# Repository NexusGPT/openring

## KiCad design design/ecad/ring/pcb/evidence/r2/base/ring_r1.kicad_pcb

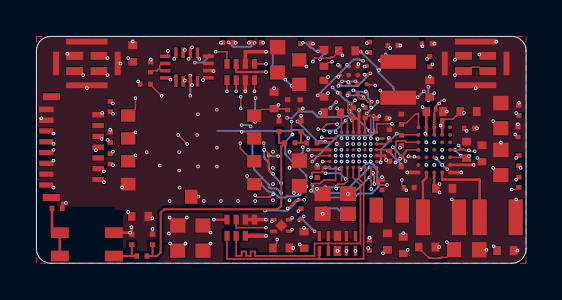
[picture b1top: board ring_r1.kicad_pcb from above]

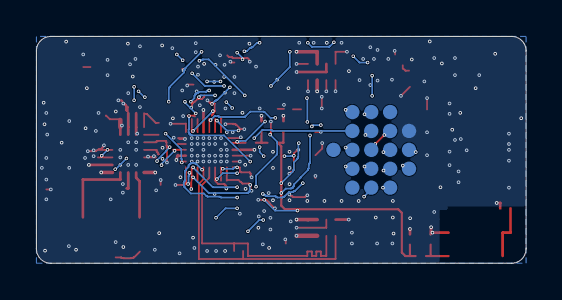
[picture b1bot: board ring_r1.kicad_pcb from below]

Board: 4 copper layers, 27.2 x 12.6 mm, 104 parts (19 on the bottom side), 91 nets.

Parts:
ANT1: 2450AT18D0100001E; ANT_Johanson_2450AT18D0100001E_3.2x1.6
C1, C2, C5, C61, C72, C80, C81, C82: 100nF; Chip_0201
C3: 1.2pF; Chip_0201
C4, C22, C74, C75, C78, C79, C83, C84: 10uF; Chip_0402
C6: 4.7uF; Chip_0201
C7, C10, C14: 2.2uF; Chip_0201
C11: 4.7uF; Chip_0402
C12: 0.5pF; Chip_0201
C13, C89: DNP; Chip_0201
C21, C26, C27: 4.7uF; Chip_0603
C23, C60, C85: 2.2uF; Chip_0402
C24, C25, C88: 10uF; Chip_0603
C28, C29: 22uF; Chip_0402
C31, C32: 1uF; Chip_0201
C35, C36: 1nF C0G; Chip_0402
C71: 1.0uF 25V; Chip_0402
C73: 1.0uF; Chip_0201
C76, C77: 1.0nF; Chip_0201
C86, C87: 1.0uF; Chip_0402
FB1: 120R@100MHz; Chip_0201
J1: FH35C-15S-0.3SHW(50); FPC_Hirose_FH35C-15S-0.3SHW
J_BAND_A: flex tail A (joystick side) 8 pads; J_BAND_A_BOARD
J_BAND_B: flex tail B (other side) 7 pads; J_BAND_B_BOARD
L1: 4.7uH; L_TDK_MLZ1608_1.6x0.8
L2: 3.6nH; Chip_0201
L3: 4.7nH; Chip_0201
L4: 3.3nH; Chip_0201
L10, L71, L72: 2.2uH; L_Murata_1269AS-H_2.5x2.0
LT1: 0R; Chip_0201
R1: 2.2R; Chip_0603
R2: 220R; Chip_0201
R31, R32, R61: 100R; Chip_0201
R57, R58: 4.7k; Chip_0201
R60, R63, R64, R65, R71: 47k; Chip_0201
R62, R66: 100k; Chip_0201
R72: 150k; Chip_0201
TP1, TP2, TP3, TP4, TP5, TP6, TP8, TP9, TP11, TP12, TP13, TP14, TP15, TP16, TP17, TP18, TP19, TP21, TP22: pad; TESTPAD_0.8
U1: nRF54LM20A; WLCSP-61_nRF54LM20A-CAAA
U2: nPM1304; WLCSP-35_nPM1304-CAAA
U3: CSNP32GCR01-BOW; LGA-9_CSNP32GCR01-BOW_8.0x6.2
U4: SGM38046; WLCSP-16_SGM38046_2.0x2.0_P0.5
U5, U6: SPK0641HT4H-1; LGA-8_Knowles_SPK0641HT4H-1_3.0x4.0
U9: TPD4E05U06; USON-10_TPD4E05U06DQA
U10: SN74AXC4T774; UQFN-16_SN74AXC4T774RSV_1.8x2.6
U11: TLV75530P 3.0V; X2SON-4_TLV755xxPDQN_1.0x1.0
X1: 32MHz; XTAL_Kyocera_CX2016DB_2.0x1.6
X2: 32.768kHz; XTAL_TXC_9HT11_2.0x1.2

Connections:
ANT1_NODE: L2.1, U1.C1
ANT2_NODE: C3.1, L2.2, L3.1
ANT3_NODE: C12.1, C89.1, L3.2, L4.1
ANT_TRIM: ANT1.2, ANT1.3, LT1.1
BTN_REC: J_BAND_A.5, U1.H2
DBG_RX: TP2.1, U1.B5
DBG_TX: TP1.1, U1.B4
DCC: L1.1, U1.A5
DECA: C7.1, C14.1, FB1.2, U1.A8, U1.B2
DECD: C6.1, FB1.1, L1.2, U1.A6
ELVDD: C25.1, J1.2, U4.D3
ELVSS: C28.1, C29.1, J1.1, U4.D4
GND: ANT1.4, C1.2, C2.2, C3.2, C4.2, C5.2, C6.2, C7.2, C10.2, C11.2, C12.2, C13.2, C14.2, C21.2, C22.2, C24.2, C25.2, C26.2, C27.2, C28.2, C29.2, C31.2, C32.2, C35.2, C36.2, C60.2, C61.2, C71.2, C72.2, C73.2, C74.2, C75.2, C76.2, C77.2, C78.2, C79.2, C80.2, C81.2, C82.2, C83.2, C84.2, C85.2, C86.2, C87.2, C88.2, C89.2, J1.13, J1.14, J1.15, J_BAND_A.6, J_BAND_A.8, J_BAND_B.2, J_BAND_B.7, LT1.2, R2.2, R62.2, R66.2, R71.2, R72.2, TP18.1, U1.A7, U1.D3, U1.E1, U1.F10, U2.A6, U2.A7, U2.E7, U3.4, U4.A3, U4.B2, U4.B3, U5.3, U5.5, U5.6, U5.7, U5.8, U6.5, U6.6, U6.7, U6.8, U9.3, U9.8, U10.6, U10.7, U10.8, U11.2, U11.5, X1.2
JOY_CENTER: TP22.1, U1.H4
JOY_DOWN: J_BAND_A.2, U1.G2
JOY_LEFT: J_BAND_A.3, U1.G1
JOY_RIGHT: J_BAND_A.4, U1.G10
JOY_UP: J_BAND_A.1, U1.H1
LCD_CS: J1.9, U1.F7
LCD_DCX: J1.11, U1.G7
LCD_MOSI: J1.12, U1.G8
LCD_RST: J1.8, U1.H5
LCD_SCK: J1.10, U1.G9
LCD_TE: J1.7, U1.D6
MIC1_DATA: R31.1, U5.1
MIC2_DATA: R32.1, U6.1
MIC_A_CLK: U1.F1, U5.2, U6.2
MIC_A_DATA: R31.2, R32.2, U1.F2
MIC_B_DATA: TP21.1, U1.D7
MOTOR: R61.1, U1.F6
MOT_EN: R61.2, R62.1, U11.3
NRESET: TP5.1, U1.E2
NTC: J_BAND_B.3, U2.D3
OLED_PWR_EN: R66.1, U1.E9, U4.C2
PMIC_INT: U1.D8, U2.D6
PMIC_SCL: R58.1, U1.E7, U2.E3
PMIC_SDA: R57.1, U1.B8, U2.E5
RF_FEED: ANT1.1, C13.1, L4.2
SDC_CS: R65.1, U3.2, U10.10
SDC_MISO: R60.1, U3.6, U10.9
SDC_MOSI: U3.5, U10.11
SDC_SCK: U3.3, U10.12
SD_CS: U1.D9, U10.3
SD_DAT1: R63.1, U3.7
SD_DAT2: R64.1, U3.1
SD_MISO: U1.D10, U10.4
SD_MOSI: U1.B10, U10.2
SD_SCK: U1.A9, U10.1
SGM_AVDD: C26.1, U4.D2
SGM_AVIN: C22.1, U4.A2
SGM_C1N: C23.2, U4.B4
SGM_C1P: C23.1, U4.A4
SGM_SW1: L10.1, U4.B1
SGM_SW2: L10.2, U4.C1
SGM_VON: C27.1, U4.C4
SGM_VOUT: C24.1, U4.D1
SHPHLD: TP19.1, U2.D4
SPARE_P1_00: TP6.1, U1.H10
SPARE_P1_02: TP8.1, U1.F8
SPARE_P1_14: TP9.1, U1.F4
SPARE_P1_30: TP11.1, U1.F9
SPARE_P2_00: TP12.1, U1.A10
SPARE_P2_03: TP13.1, U1.B9
SPARE_P3_03: TP14.1, U1.F5
SPARE_P3_04: TP15.1, U1.G5
SPARE_P3_05: TP16.1, U1.G4
SW1: L71.1, U2.B7
SW2: L72.1, U2.D7
SWDCLK: TP3.1, U1.D5
SWDIO: TP4.1, U1.E4
SWIRE: J1.6, U4.C3
TXRTUNE: R2.1, U1.G6
U1_VBUS: C11.1, R1.2, U1.H9
USB_DN: J_BAND_B.5, U1.H6, U9.2
USB_DP: J_BAND_B.6, U1.H7, U9.1
VBAT: C21.1, C83.1, C85.1, J_BAND_B.1, U2.D1, U2.D2, U4.A1, U11.4
VBUS: C71.1, C72.1, J_BAND_B.4, R1.1, U2.B1, U2.B2, U9.4, U9.5
VBUSOUT: C73.1, U2.C3
VDD_1V8: C1.1, C2.1, C4.1, C5.1, C78.1, C80.1, C81.1, J1.5, L71.2, R57.2, R58.2, TP17.1, U1.A4, U1.E10, U2.B4, U2.B6, U2.E4, U10.5, U10.14, U10.15, U10.16
VDD_3V0: C79.1, J1.4, L72.2, U2.B5, U2.C6
VDD_MIC: C31.1, C32.1, C35.1, C36.1, C86.1, U2.A4, U5.4, U6.3, U6.4
VDD_SD: C60.1, C61.1, C82.1, C87.1, R60.2, R63.2, R64.2, R65.2, U2.A5, U3.8, U10.13
VDD_USB_3V3: C10.1, U1.H8
VMOT: C84.1, J_BAND_A.7, U11.1
VSET1: R71.1, U2.E2
VSET2: R72.1, U2.E1
VSYS: C74.1, C75.1, C76.1, C77.1, C88.1, U2.C1, U2.C2, U2.C7
XC1: U1.A2, X1.1
XC2: U1.A1, X1.3
XL1: U1.B6, X2.1
XL2: U1.B7, X2.2

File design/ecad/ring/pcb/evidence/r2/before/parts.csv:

reference,symbol,value,mpn,footprint,sheet,dnp
U1,nRF54LM20A_CAAA,nRF54LM20A,NRF54LM20A-CAAA-R7,OpenRing:WLCSP-61_nRF54LM20A-CAAA,main,no
C4,C,10uF,GRM155R60J106ME15D,OpenRing:Chip_0402,main,no
C5,C,100nF,CL03A104KP3NNNC,OpenRing:Chip_0201,main,no
C1,C,100nF,CL03A104KP3NNNC,OpenRing:Chip_0201,main,no
C2,C,100nF,CL03A104KP3NNNC,OpenRing:Chip_0201,main,no
L1,L,4.7uH,MLZ1608M4R7WT000,OpenRing:L_TDK_MLZ1608_1.6x0.8,main,no
C6,C,4.7uF,GRM035R60J475ME15J,OpenRing:Chip_0201,main,no
FB1,FB,120R@100MHz,BLM03AG121SN1D,OpenRing:Chip_0201,main,no
C7,C,2.2uF,GRM033D80E225ME47D,OpenRing:Chip_0201,main,no
C14,C,2.2uF,GRM033D80E225ME47D,OpenRing:Chip_0201,main,no
C10,C,2.2uF,GRM033D80E225ME47D,OpenRing:Chip_0201,main,no
R1,R,2.2R,RC0603FR-072R2L,OpenRing:Chip_0603,main,no
C11,C,4.7uF,GRM155R61A475MEAAD,OpenRing:Chip_0402,main,no
R2,R,220R,RC0201FR-07220RL,OpenRing:Chip_0201,main,no
X1,XTAL_CX2016DB,32MHz,CX2016DB32000D0WZRC1,OpenRing:XTAL_Kyocera_CX2016DB_2.0x1.6,main,no
X2,XTAL_2PAD,32.768kHz,9HT11-32.768KDZC-T,OpenRing:XTAL_TXC_9HT11_2.0x1.2,main,no
L2,L,3.6nH,LQP03HQ3N6B02,OpenRing:Chip_0201,main,no
C3,C,1.2pF,GJM0335C1H1R2WB01D,OpenRing:Chip_0201,main,no
L3,L,4.7nH,LQP03HQ4N7H02,OpenRing:Chip_0201,main,no
C12,C,0.5pF,GJM0335C1ER50WB01D,OpenRing:Chip_0201,main,no
L4,L,3.3nH,LQP03HQ3N3B02,OpenRing:Chip_0201,main,no
C13,C,DNP,,OpenRing:Chip_0201,main,yes
ANT1,2450AT18D0100,2450AT18D0100001E,2450AT18D0100001E,OpenRing:ANT_Johanson_2450AT18D0100001E_3.2x1.6,main,no
LT1,R,0R,,OpenRing:Chip_0201,main,no
C89,C,DNP,,OpenRing:Chip_0201,main,yes
U2,nPM1304_CSP35,nPM1304,nPM1304-CAAA-R7,OpenRing:WLCSP-35_nPM1304-CAAA,power,no
C71,C,1.0uF 25V,GRM155R61E105KA12D,OpenRing:Chip_0402,power,no
C85,C,2.2uF,0402ZC225KAT2A,OpenRing:Chip_0402,power,no
C88,C,10uF,GRT188R61A106KE13D,OpenRing:Chip_0603,power,no
C86,C,1.0uF,GRM155R61E105KA12D,OpenRing:Chip_0402,power,no
C87,C,1.0uF,GRM155R61E105KA12D,OpenRing:Chip_0402,power,no
C72,C,100nF,CL03A104KP3NNNC,OpenRing:Chip_0201,power,no
C73,C,1.0uF,GRM033R60J105MEA2D,OpenRing:Chip_0201,power,no
C74,C,10uF,GRM155R60J106ME15D,OpenRing:Chip_0402,power,no
C75,C,10uF,GRM155R60J106ME15D,OpenRing:Chip_0402,power,no
C76,C,1.0nF,,OpenRing:Chip_0201,power,no
C77,C,1.0nF,,OpenRing:Chip_0201,power,no
L71,L,2.2uH,1269AS-H-2R2M=P2,OpenRing:L_Murata_1269AS-H_2.5x2.0,power,no
C78,C,10uF,GRM155R60J106ME15D,OpenRing:Chip_0402,power,no
L72,L,2.2uH,1269AS-H-2R2M=P2,OpenRing:L_Murata_1269AS-H_2.5x2.0,power,no
C79,C,10uF,GRM155R60J106ME15D,OpenRing:Chip_0402,power,no
C80,C,100nF,CL03A104KP3NNNC,OpenRing:Chip_0201,power,no
R71,R,47k,RC0201FR-0747KL,OpenRing:Chip_0201,power,no
R72,R,150k,RC0201FR-07150KL,OpenRing:Chip_0201,power,no
RT1,NTC,10k NTC,NCP15XH103F03RC,OpenRingBand:RT1_NTC_0402,band,no
BT1,CELL,4.35V 20-27mAh at US9 (17.6mAh min at US7) curved,Grepow custom,OpenRingBand:PRT1_Tabs,band,no
R57,R,4.7k,RC0201FR-074K7L,OpenRing:Chip_0201,power,no
R58,R,4.7k,RC0201FR-074K7L,OpenRing:Chip_0201,power,no
U5,SPK0641HT4H_1,SPK0641HT4H-1,SPK0641HT4H-1,OpenRing:LGA-8_Knowles_SPK0641HT4H-1_3.0x4.0,mics,no
R31,R,100R,RC0201FR-07100RL,OpenRing:Chip_0201,mics,no
C31,C,1uF,GRM033R60J105MEA2D,OpenRing:Chip_0201,mics,no
C35,C,1nF C0G,04025A102JAT2A,OpenRing:Chip_0402,mics,no
U6,SPK0641HT4H_1,SPK0641HT4H-1,SPK0641HT4H-1,OpenRing:LGA-8_Knowles_SPK0641HT4H-1_3.0x4.0,mics,no
R32,R,100R,RC0201FR-07100RL,OpenRing:Chip_0201,mics,no
C32,C,1uF,GRM033R60J105MEA2D,OpenRing:Chip_0201,mics,no
C36,C,1nF C0G,04025A102JAT2A,OpenRing:Chip_0402,mics,no
U3,CSNP32GCR01_BOW,CSNP32GCR01-BOW,CSNP32GCR01-BOW,OpenRing:LGA-9_CSNP32GCR01-BOW_8.0x6.2,storage,no
U10,SN74AXC4T774_RSV,SN74AXC4T774,SN74AXC4T774RSVR,OpenRing:UQFN-16_SN74AXC4T774RSV_1.8x2.6,storage,no
C81,C,100nF,CL03A104KP3NNNC,OpenRing:Chip_0201,storage,no
C82,C,100nF,CL03A104KP3NNNC,OpenRing:Chip_0201,storage,no
R60,R,47k,RC0201FR-0747KL,OpenRing:Chip_0201,storage,no
R63,R,47k,RC0201FR-0747KL,OpenRing:Chip_0201,storage,no
R64,R,47k,RC0201FR-0747KL,OpenRing:Chip_0201,storage,no
R65,R,47k,RC0201FR-0747KL,OpenRing:Chip_0201,storage,no
C60,C,2.2uF,0402ZC225KAT2A,OpenRing:Chip_0402,storage,no
C61,C,100nF,CL03A104KP3NNNC,OpenRing:Chip_0201,storage,no
U4,SGM38046,SGM38046,SGM38046YG/TR,OpenRing:WLCSP-16_SGM38046_2.0x2.0_P0.5,screen,no
L10,L,2.2uH,1269AS-H-2R2M=P2,OpenRing:L_Murata_1269AS-H_2.5x2.0,screen,no
C21,C,4.7uF,GRM188R61C475KAAJD,OpenRing:Chip_0603,screen,no
C22,C,10uF,GRM155R60J106ME15,OpenRing:Chip_0402,screen,no
C23,C,2.2uF,GRM155R60J225ME15,OpenRing:Chip_0402,screen,no
C24,C,10uF,GRM188R61C106KAALD,OpenRing:Chip_0603,screen,no
C25,C,10uF,GRM188R61C106KAALD,OpenRing:Chip_0603,screen,no
C26,C,4.7uF,GRM188R61C475KAAJD,OpenRing:Chip_0603,screen,no
C27,C,4.7uF,GRM188R61C475KAAJD,OpenRing:Chip_0603,screen,no
C28,C,22uF,GRM155R60J226ME11D,OpenRing:Chip_0402,screen,no
C29,C,22uF,GRM155R60J226ME11D,OpenRing:Chip_0402,screen,no
R66,R,100k,RC0201FR-07100KL,OpenRing:Chip_0201,screen,no
J1,FPC_15,FH35C-15S-0.3SHW(50),FH35C-15S-0.3SHW(50),OpenRing:FPC_Hirose_FH35C-15S-0.3SHW,screen,no
DISP1,TOH095XVT-01,TOH095XVT-01,TOH095XVT-01,OpenRing:FPCtail_Tailor_TOH095XVT-01_15,screen,no
J_BAND_A,BAND_PADS_A,flex tail A (joystick side) 8 pads,,OpenRingBand:J_BAND_A_BOARD,band,no
J_BAND_B,BAND_PADS_B,flex tail B (other side) 7 pads,,OpenRingBand:J_BAND_B_BOARD,band,no
SW1,SKTAAAE010,SKTAAAE010,SKTAAAE010,OpenRingBand:Alps_SKTAAAE010_4pad,band,no
SW2,SKTAAAE010,SKTAAAE010,SKTAAAE010,OpenRingBand:Alps_SKTAAAE010_4pad,band,no
SW3,SKTAAAE010,SKTAAAE010,SKTAAAE010,OpenRingBand:Alps_SKTAAAE010_4pad,band,no
SW4,SKTAAAE010,SKTAAAE010,SKTAAAE010,OpenRingBand:Alps_SKTAAAE010_4pad,band,no
SW5,SKTAAAE010,SKTAAAE010,SKTAAAE010,OpenRingBand:Alps_SKTAAAE010_4pad,band,no
M1,MOTOR,W0525AB001D,W0525AB001D,OpenRingBand:W0525AB001D_Lands,band,no
U11,TLV75530P_DQN,TLV75530P 3.0V,TLV75530PDQNR,OpenRing:X2SON-4_TLV755xxPDQN_1.0x1.0,controls,no
C83,C,10uF,GRM155R60J106ME15,OpenRing:Chip_0402,controls,no
C84,C,10uF,GRM155R60J106ME15,OpenRing:Chip_0402,controls,no
R61,R,100R,RC0201FR-07100RL,OpenRing:Chip_0201,controls,no
R62,R,100k,RC0201FR-07100KL,OpenRing:Chip_0201,controls,no
CP1,CONTACTPAD_VBUS,gold pad 1.6mm,,OpenRingBand:CP_Pad_1.6,band,no
CP2,CONTACTPAD,gold pad 1.6mm,,OpenRingBand:CP_Pad_1.6,band,no
CP3,CONTACTPAD,gold pad 1.6mm,,OpenRingBand:CP_Pad_1.6,band,no
CP4,CONTACTPAD,gold pad 1.6mm,,OpenRingBand:CP_Pad_1.6,band,no
U9,TPD4E05U06,TPD4E05U06,TPD4E05U06DQAR,OpenRing:USON-10_TPD4E05U06DQA,contacts,no
TP1,TESTPAD,pad,,OpenRing:TESTPAD_0.8,contacts,no
TP2,TESTPAD,pad,,OpenRing:TESTPAD_0.8,contacts,no
TP3,TESTPAD,pad,,OpenRing:TESTPAD_0.8,contacts,no
TP4,TESTPAD,pad,,OpenRing:TESTPAD_0.8,contacts,no
TP5,TESTPAD,pad,,OpenRing:TESTPAD_0.8,contacts,no
TP6,TESTPAD,pad,,OpenRing:TESTPAD_0.8,contacts,no
TP8,TESTPAD,pad,,OpenRing:TESTPAD_0.8,contacts,no
TP9,TESTPAD,pad,,OpenRing:TESTPAD_0.8,contacts,no
TP11,TESTPAD,pad,,OpenRing:TESTPAD_0.8,contacts,no
TP12,TESTPAD,pad,,OpenRing:TESTPAD_0.8,contacts,no
TP13,TESTPAD,pad,,OpenRing:TESTPAD_0.8,contacts,no
TP14,TESTPAD,pad,,OpenRing:TESTPAD_0.8,contacts,no
TP15,TESTPAD,pad,,OpenRing:TESTPAD_0.8,contacts,no
TP16,TESTPAD,pad,,OpenRing:TESTPAD_0.8,contacts,no
TP17,TESTPAD,pad,,OpenRing:TESTPAD_0.8,contacts,no
TP18,TESTPAD,pad,,OpenRing:TESTPAD_0.8,contacts,no
TP19,TESTPAD,pad,,OpenRing:TESTPAD_0.8,contacts,no
TP21,TESTPAD,pad,,OpenRing:TESTPAD_0.8,contacts,no
TP22,TESTPAD,pad,,OpenRing:TESTPAD_0.8,contacts,no
